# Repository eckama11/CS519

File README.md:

CS519
=====

Electric Imp

I am currently working on sensors to use with the Electric Imp

The electric imp website can be found at 

https://electricimp.com/

Most of the parts are from the following website

https://www.sparkfun.com/

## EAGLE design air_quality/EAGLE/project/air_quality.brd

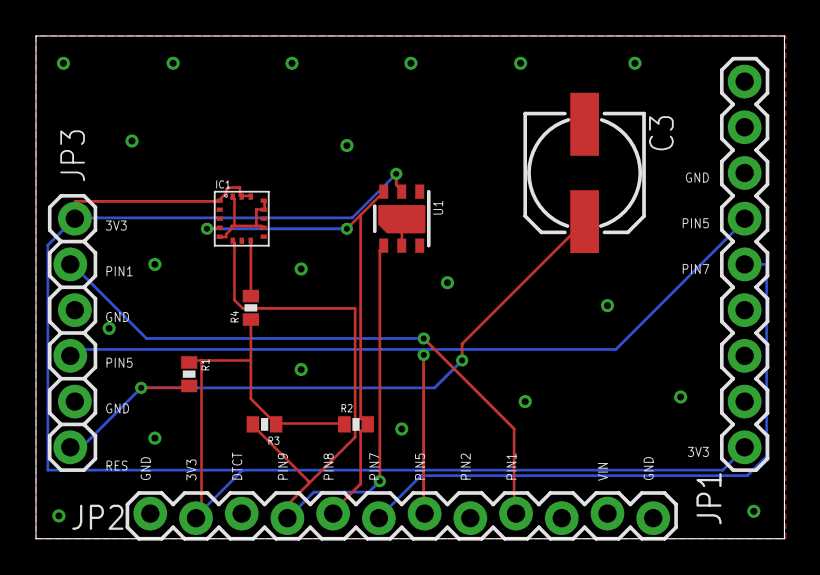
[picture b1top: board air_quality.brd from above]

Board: 2 copper layers, 41.6 x 27.9 mm, 10 parts (0 on the bottom side), 9 nets.

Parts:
C3: 220uF 16V .248 dia; 153CLV-0605
IC1: LPS331AP; HCLGA-16L
JP1: M09; 1X09
JP2: M12LOCK; 1X12_LOCK
JP3: 1X06_LOCK
R1: 150Ohm; 0402-RES
R2, R3, R4: 4.7KOhm; 0402-RES
U1: HTU21DSMD; HTU21D

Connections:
3V3: IC1.1, IC1.14, IC1.15, JP1.9, JP2.2, JP3.6, R1.1, R2.1, R3.1, R4.1, U1.VDD
CS: IC1.8, R4.2
GND: C3.-, IC1.5, IC1.10, IC1.12, IC1.13, IC1.16, JP1.3, JP2.1, JP2.12, JP3.2, JP3.4, U1.7, U1.GND
PIN1: JP2.9, JP3.5
PIN5: JP1.4, JP2.7, JP3.3
PIN7: JP1.5, JP2.6
PIN8: IC1.4, JP2.5, R2.2, U1.SCK
PIN9: IC1.6, JP2.4, R3.2, U1.DATA
RES: C3.+, JP3.1, R1.2

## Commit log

2014-02-07 TMP102
    This file shows temperature from tmp102 I2C device. Needs to be checked
    for unnecessary lines.
2014-02-10 UART SerLCD
    This describes a basic program for Squirrel and April breakout board
    and electric imp for LCD screen writing
2014-02-10 Update UART SerLCD
2014-02-10 Full UART SERLCD
    This program has ability to change brightness, scroll, splash screen,
    toggle, and more for LCD Screens.
2014-02-10 Update TMP102
2014-02-12 Create HTU21D
    Small program to get sensor to read out temp and humidity.
2014-02-14 Update HTU21D
2014-02-14 Create FullSerLCD
2014-02-14 Create ShortSerLCD
2014-02-14 Rename HTU21D to HTU21D/short
2014-02-14 Rename TMP102 to TMP102/short
2014-02-20 Create small
    this code doesn't work at the moment reading -1 for read
2014-02-20 update GPSsmall
    updated changes from electric imp forum suggestions
2014-02-20 variables changes
    asce characters don't like internet pasting and temp needs to be a
    global variable
2014-02-21 xively updates
    this consist of 2 files one for agent code and one for device code
2014-02-21 working small code
    took out extra lines not needed
2014-02-28 Using LCD to read out values
    Pairing humidity and temp sensors to an LCD to read out information.
2014-03-01 agent code
    This is the agent code to send message to LCD based on http requests strings
2014-03-01 device code
    This code allows http requests to be sent and messages written to LCD
2014-03-05 Create short
    not functioning properly. reading out 201 deg F for instance
2014-03-06 Update short
    Changed pressure to be in inHg also edited altitude function
2014-03-07 Update short
    fixes pressure reading but temp still does not work
2014-03-07 Update short
    comment out temp, server.log altitude
2014-03-12 Create project
    this is file for project HTU21D, altitude, and dust sensor
2014-03-12 Update project
    server stuff
2014-03-12 Create agent
    agent code
2014-03-12 Create device
    device code
2014-03-12 Delete project
    created air_quality folder to house this
2014-03-12 Update agent
    fix agent logging
2014-03-13 fix agent
    agent was pasted incorrectly
2014-03-14 Concat temp/hum/altitude/pressure
    makes file smaller and keeps all functions
2014-03-14 fix bug
    git hub issues
2014-03-21 modify device
    added hardware.disable for GPS. Also now calls back to agent to give lat and long coordinates. All sensors working pressure/altitude/temperature/humidity.
2014-03-21 Modify Agent
    added GPS calls to send reply to server.
2014-03-24 Create air_quality.sql
    file to add air_quality sql tables
2014-03-24 modify air_quality/device
    took out extra spaces and included more comments
2014-03-24 modify sql
    sql does not allow Decimal(M,N) to have M less than N
2014-03-24 create CodeIgnitor files
    Created code ignitor files
2014-03-24 modify database
    drop database if exists air_quality;
2014-03-24 modify sql
    drop user and rebuild if exists
2014-03-26 create PIR sensor file
    small sensor file to see if sensor activated and read out value from
    electric imp light sensor
2014-03-26 create small Dust sensor file
    working but not reading good values for voltage
2014-03-27 Update air_quality.sql
    loginsession sql
2014-03-27 Update air_quality.sql
    create user table
2014-03-27 Update air_quality.sql
    authenticatedEmployee to authenticatedUser and move user above loginSession
2014-03-28 Update air_quality.sql
    not doing deactivate users
2014-03-28 made page to view things from with login
2014-03-28 modify dust sensor
    fixed algorithm for dust density. Only accurate up to .4 mg/m^3 and 3
    volts.
2014-03-29 Update air_quality.sql
    added particle col
2014-03-31 modify dust common page
    change name for Air Quality
2014-03-31 Update agent
    sending to server
2014-03-31 Update device
    updated for server
2014-04-02 Modify Add.php
    added product number to account
2014-04-02 modify add and doAdd
    updated adding user to database will still need to add methods to add
    user to device table too.
2014-04-10 modify
    changes dbinterface, common.php
2014-04-10 Update air_quality.sql
    -modified User to have email.
    -created imp table to keep track of multiple imps for one user.
    -created sensors table while deleting other tables to create one place to keep all measurements based on time stamp date.
2014-04-11 Update air_quality.sql
    keeping classes and tables consistent
2014-04-11 Update air_quality.sql
    Device ID is determined by electric imp not database.
2014-04-11 add email to User
    - DBInterface modified to add user email, and Device class interaction
    - Device class added for DB updates in future iteration
    - User updated to include email
2014-04-11 modify
    delete email check
2014-04-11 modify
    - program now adds new users
    - still need to implement adding devices and userId to DB
2014-04-11 modify
    - DBInterface added writeDevice ability
    - Device fixed bug
    -doAdd added device db insertion
    - page changed the user options for future addition of adding devices
2014-04-14 modify bug
    - U Pay changed to Air Quality
2014-04-15 Update air_quality.sql
    deleted device table. Added device to user table.
2014-04-15 Update air_quality.sql
    bug fix
2014-04-15 modify 519.sql and classes
    - user now includes device, sql user table includes device
    - device class deleted, and sql table deleted
2014-04-16 Update air_quality.sql
    deviceId to device
2014-04-25 add schematic and board
    included EAGLE files for
    board
    schematic
    rules for OSH park .dru
    Bill of Materials file
2014-04-25 modify air_quality
2014-04-25 Update device
    added dust sensor and moved other sensors to accommodate.
2014-04-25 Update agent
    device now only goes to one site page
2014-04-25 delete code ignitor
    not using code ignitor files at this time
2014-04-25 Update Bill_of_Materials
2014-04-25 add digikey specific specifications
    description for resistors and capacitor used for pc board
2014-04-30 modify weeks worth of effort
    kept in 2 different places, finally updating
2014-06-06 modify bug for password reset
    added username for reset in UPDATE statement.

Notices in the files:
parts and their libraries:
SparkFun-Sensors: Licensing: Creative Commons ShareAlike 4.0 International - https://creativecommons.org/licenses/by-sa/4.0
